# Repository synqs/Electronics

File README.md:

This project is licensed under the terms of the MIT license.

# Electronics in SynQS 

Here we have several electronics projects. Feel free to use and improve them.

## balancedphotodiode

It was used for a balanced PD design
in a polarization spectroscopy and worked fine. Designed initially by Lilo Höcker.

## simplePDboard

Just a simple board to have a transimpedence attached to the normal OSRAM PD.

## MagneticFieldSensor

We should add this here as it was the main project to the 18bit DAC and the 
digi-poti adapter. Designed initially by Marcell Gall.

## AOM_powersupply

A board which allows to drive a combination of VCO, attenuator, switch and amplifier. Designed initially by Pradyumna Paranjabe.

## shutter_board

A simple board to control a relay shutter. Designed initially by Pradyumna Paranjabe.

## others

the other projects were created before.

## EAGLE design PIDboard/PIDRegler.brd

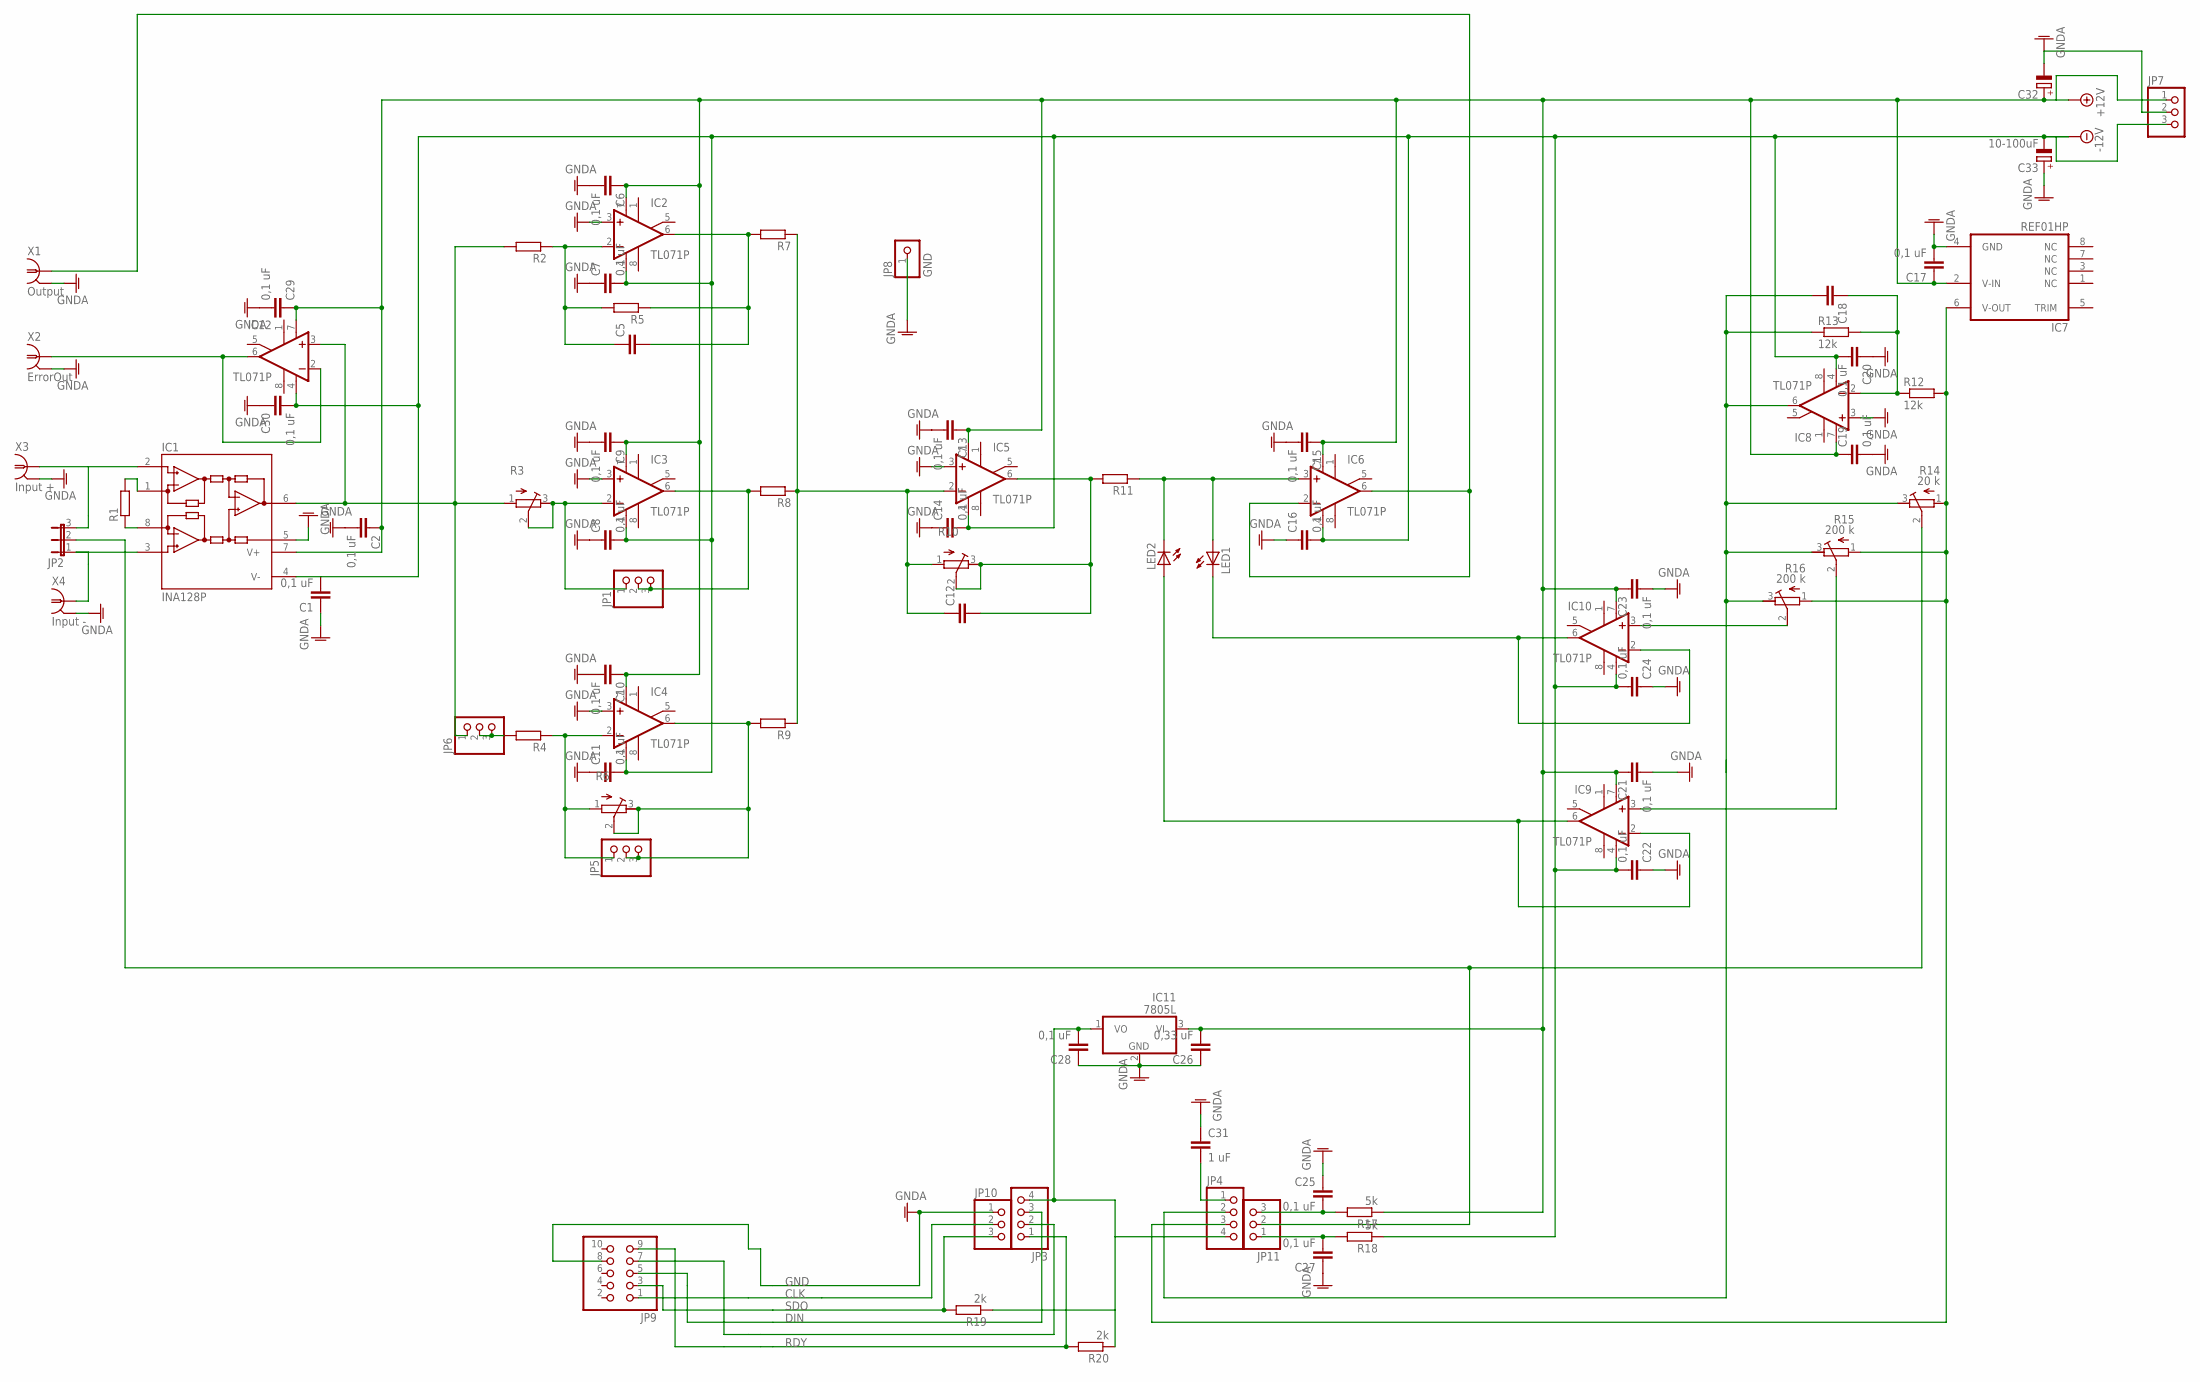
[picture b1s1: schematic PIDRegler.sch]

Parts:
C1, C2, C6, C7, C8, C9, C10, C11, C13, C14, C15, C16, C17, C19, C20, C21, C22, C23, C24, C25, C27, C28, C29, C30: 0,1 uF; C1206
C5, C12, C18: C-EUC1206; C1206
C26: 0,33 uF; C1206
C31: 1 uF; C1206
C32: CPOL-EUE2.5-6; E2,5-6
C33: 10-100uF; E2,5-6
IC1: INA128P; DIL08
IC2, IC3, IC4, IC5, IC6, IC8, IC9, IC10, IC12: TL071P; DIL08
IC7: REF01HP; DIL08
IC11: 7805L; TO92
JP1, JP5, JP6, JP7, JP10, JP11: PINHD-1X3; 1X03
JP2: JP2E; JP2
JP3, JP4: PINHD-1X4; 1X04
JP8: GND; 1X01
JP9: PINHD-2X5; 2X05
LED1, LED2: LED5MM
R1, R2, R4, R5, R7, R8, R9, R11: R-EU_M1206; M1206
R3, R6, R10: R-TRIMM64X; RTRIM64X
R12, R13: 12k; M1206
R14: 20 k; RTRIM64X
R15, R16: 200 k; RTRIM64X
R17, R18: 5k; M1206
R19, R20: 2k; M1206
X1: Output; AMP_227161
X2: ErrorOut; AMP_227161
X3: Input +; AMP_227161
X4: Input -; AMP_227161

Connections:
+12V: C2.1, C6.1, C9.1, C10.1, C13.1, C15.1, C17.1, C19.1, C21.1, C23.1, C26.2, C29.1, C32.+, IC1.7 (V+), IC2.7 (V+), IC3.7 (V+), IC4.7 (V+), IC5.7 (V+), IC6.7 (V+), IC7.2 (V-IN), IC8.7 (V+), IC9.7 (V+), IC10.7 (V+), IC11.3 (VI), IC12.7 (V+), JP7.1, R17.1
-12V: C1.2, C7.2, C8.2, C11.2, C14.2, C16.2, C20.2, C22.2, C24.2, C30.2, C33.-, IC1.4 (V-), IC2.4 (V-), IC3.4 (V-), IC4.4 (V-), IC5.4 (V-), IC6.4 (V-), IC8.4 (V-), IC9.4 (V-), IC10.4 (V-), IC12.4 (V-), JP7.3, R18.1
CLK: JP9.1, JP10.2
DIN: JP3.3, JP9.5
GND: C1.1, C2.2, C6.2, C7.1, C8.1, C9.2, C10.2, C11.1, C13.2, C14.1, C15.2, C16.1, C17.2, C19.2, C20.1, C21.2, C22.1, C23.2, C24.1, C25.1, C26.1, C27.1, C28.1, C29.2, C30.1, C31.1, C32.-, C33.+, IC1.5 (REF), IC2.3 (+IN), IC3.3 (+IN), IC4.3 (+IN), IC5.3 (+IN), IC7.4 (GND), IC8.3 (+IN), IC11.2 (GND), JP7.2, JP8.1, JP9.8, JP10.1, X1.2 (GND), X2.2 (GND), X3.2 (GND), X4.2 (GND)
unnamed: IC1.3 (+IN), JP2.1, X4.1
unnamed: IC1.8 (RG), R1.1
unnamed: IC1.1 (RG), R1.2
unnamed: IC1.2 (-IN), JP2.3, X3.1
unnamed: IC1.6 (OUT), IC12.3 (+IN), JP6.1, R2.2, R3.1 (E)
unnamed: IC3.2 (-IN), JP1.1, R3.2 (S), R3.3 (A)
unnamed: JP6.2, JP6.3, R4.2
unnamed: C5.1, IC2.2 (-IN), R2.1, R5.2
unnamed: C12.1, IC5.2 (-IN), R7.1, R8.1, R9.1, R10.1 (E)
unnamed: C5.2, IC2.6 (OUT), R5.1, R7.2
unnamed: IC3.6 (OUT), JP1.2, JP1.3, R8.2
unnamed: IC4.6 (OUT), JP5.2, JP5.3, R6.2 (S), R6.3 (A), R9.2
unnamed: C12.2, IC5.6 (OUT), R10.2 (S), R10.3 (A), R11.2
unnamed: IC6.2 (-IN), IC6.6 (OUT), X1.1
unnamed: IC7.6 (V-OUT), JP4.3, R12.2, R14.1 (E), R15.1 (E), R16.1 (E)
unnamed: JP2.2, JP11.2, R14.2 (S)
unnamed: C18.1, IC8.2 (-IN), R12.1, R13.2
unnamed: IC4.2 (-IN), JP5.1, R4.1, R6.1 (E)
unnamed: IC10.2 (-IN), IC10.6 (OUT), LED1.K (C)
unnamed: IC9.3 (+IN), R15.2 (S)
unnamed: IC9.2 (-IN), IC9.6 (OUT), LED2.A
unnamed: IC10.3 (+IN), R16.2 (S)
unnamed: IC6.3 (+IN), LED1.A, LED2.K (C), R11.1
unnamed: C31.2, JP4.1
unnamed: IC12.2 (-IN), IC12.6 (OUT), X2.1
unnamed: C18.2, IC8.6 (OUT), JP4.2, R13.1, R14.3 (A), R15.3 (A), R16.3 (A)
unnamed: C25.2, JP11.3, R17.2
unnamed: C27.2, JP11.1, R18.2
RDY: JP3.1, JP9.9, R20.2
SDO: JP9.3, JP10.3, R19.2
SYNC: JP3.2, JP9.7
VCC: C28.2, IC11.1 (VO), JP3.4, JP4.4, R19.1, R20.1

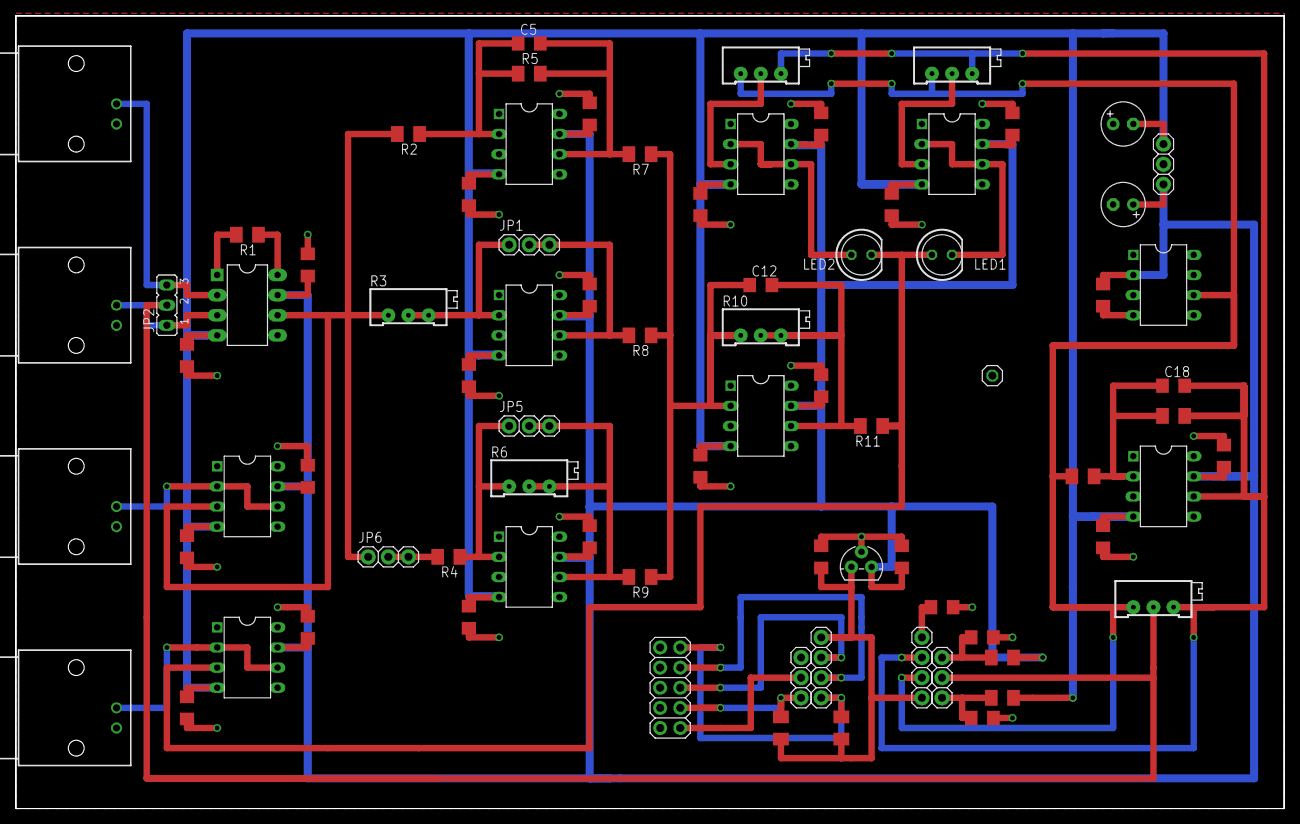
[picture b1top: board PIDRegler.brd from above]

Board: 2 copper layers, 160.0 x 100.0 mm, 80 parts (0 on the bottom side), 37 nets.

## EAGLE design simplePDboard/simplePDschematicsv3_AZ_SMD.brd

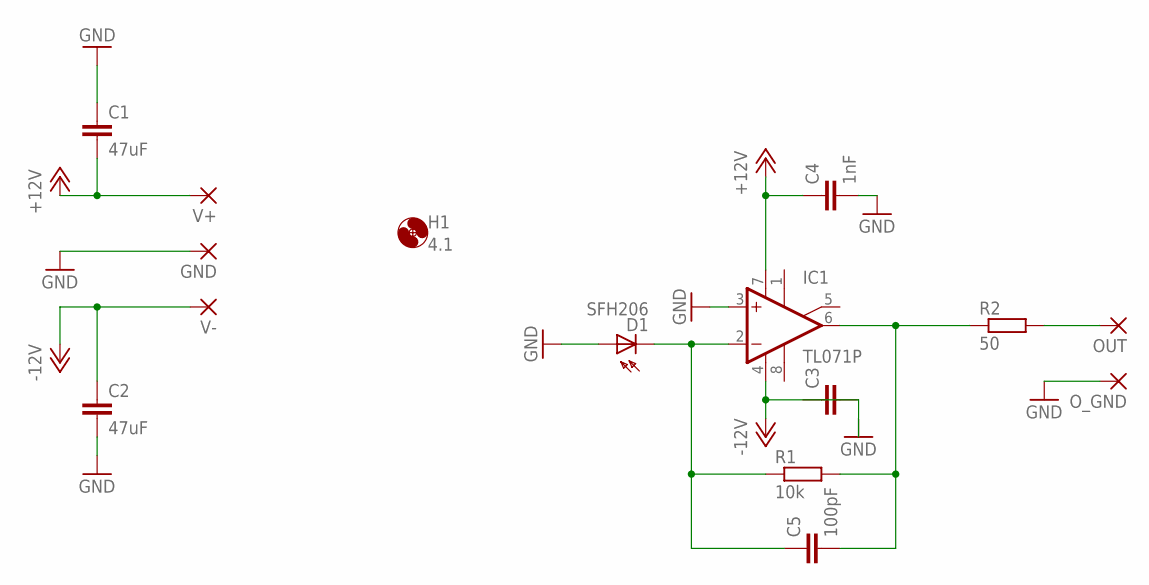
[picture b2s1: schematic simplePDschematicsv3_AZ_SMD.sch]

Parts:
C1, C2: 47uF; C050-075X075
C3: C-EUC0504; C0504
C4: 1nF; C025-050X050
C5: 100pF; C025-050X050
D1: SFH206
GND: 1,6/0,9
H1: 4.1; 4,1
IC1: TL071P; DIL08
OUT: 1,6/0,9
O_GND: 1,6/0,9
R1: 10k; M1206
R2: 50; M1206
V+: 1,6/0,9
V-: 1,6/0,9

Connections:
GND: C1.1, C2.2, C4.2, D1.A, GND.1, IC1.3 (+IN), O_GND.1
unnamed: OUT.1, R2.2
unnamed: C5.2, IC1.6 (OUT), R1.2, R2.1
unnamed: C5.1, D1.K (C), IC1.2 (-IN), R1.1
V+: C1.2, C4.1, IC1.7 (V+), V+.1
V-: C2.1, IC1.4 (V-), V-.1

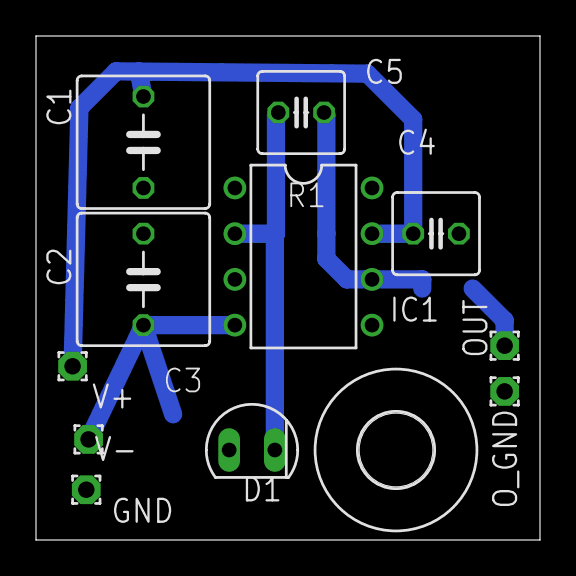
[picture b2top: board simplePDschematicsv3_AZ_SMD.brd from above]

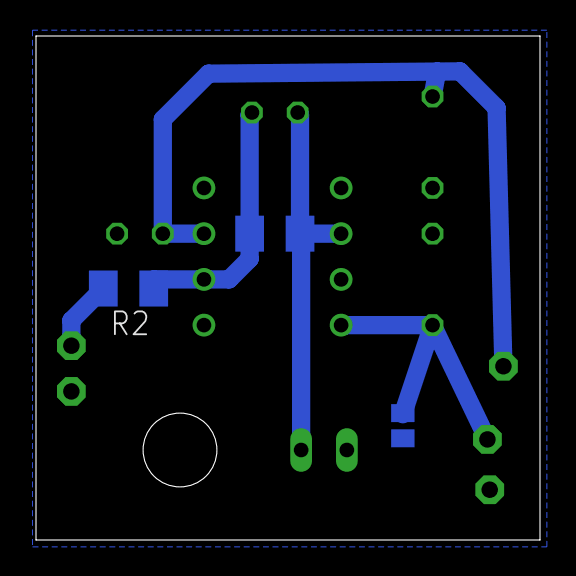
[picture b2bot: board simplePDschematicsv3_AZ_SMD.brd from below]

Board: 2 copper layers, 28.0 x 28.0 mm, 15 parts (3 on the bottom side), 6 nets.

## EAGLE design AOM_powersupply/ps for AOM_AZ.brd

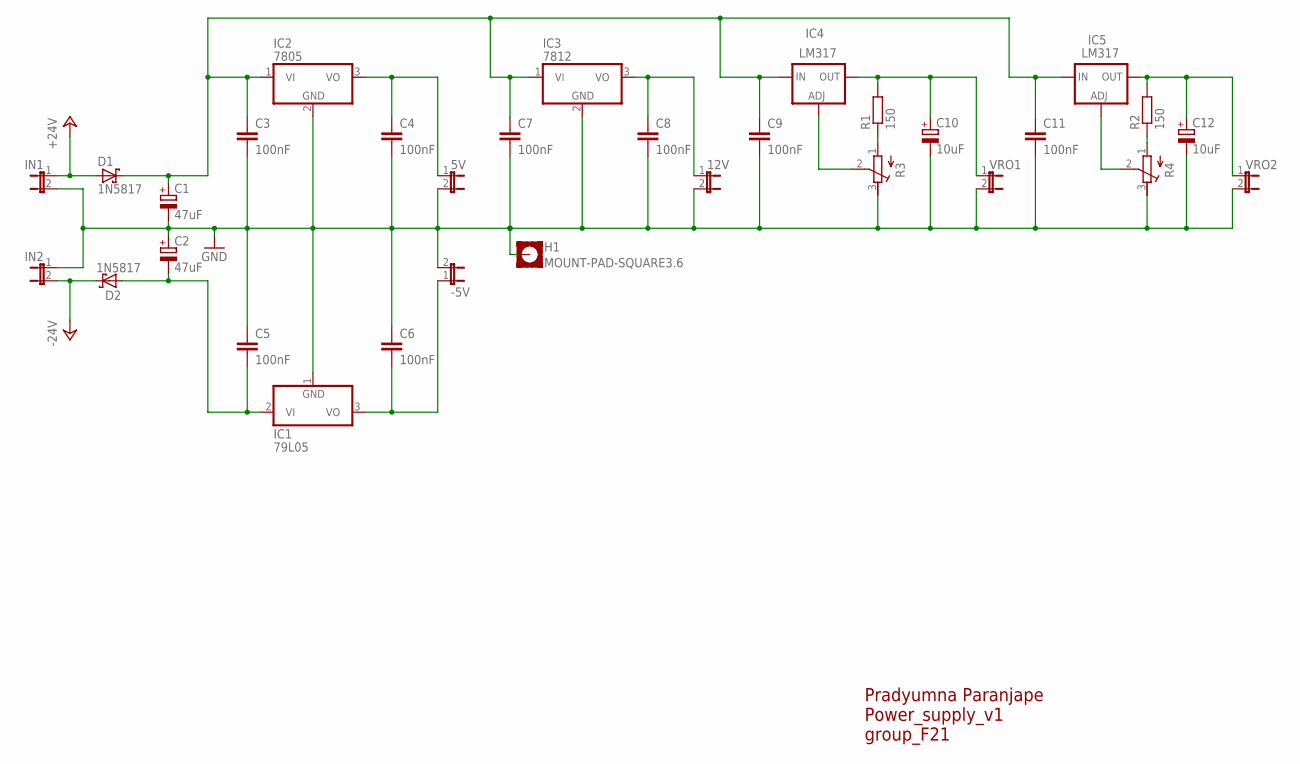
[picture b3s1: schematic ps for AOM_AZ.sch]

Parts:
5V, 12V: JP1E; JP1
-5V: JP1E; JP1
C1, C2: 47uF; E5-6
C3, C4, C5, C6, C7, C8, C9, C11: 100nF; C1206K
C10, C12: 10uF; E1,8-4
D1, D2: 1N5817; DO41-7.6
H1: MOUNT-PAD-SQUARE3.6; 3,6-PAD-SQUARE
IC1: 79L05; TO92
IC2: 7805; TO220H
IC3: 7812; TO220H
IC4, IC5: LM317; TO220H
IN1, IN2: JP1E; JP1
R1, R2: 150; R1206
R3, R4: R-TRIMM3296Y; RTRIM3296Y
VRO1, VRO2: JP1E; JP1

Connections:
+24V: D1.A, IN1.1
+VS: C1.+, C3.1, C7.1, C9.1, C11.1, D1.C, IC2.1 (VI), IC3.1 (VI), IC4.3 (IN), IC5.3 (IN)
-24V: D2.C, IN2.2
-VS: C2.-, C5.2, D2.A, IC1.2 (VI)
GND: 5V.2, 12V.2, -5V.2, C1.-, C2.+, C3.2, C4.2, C5.1, C6.1, C7.2, C8.2, C9.2, C10.-, C11.2, C12.-, H1.B3,6, IC1.1 (GND), IC2.2 (GND), IC3.2 (GND), IN1.2, IN2.1, R3.3 (E), R4.3 (E), VRO1.2, VRO2.2
unnamed: C12.+, IC5.2 (OUT), R2.2, VRO2.1
unnamed: 12V.1, C8.1, IC3.3 (VO)
unnamed: 5V.1, C4.1, IC2.3 (VO)
unnamed: -5V.1, C6.2, IC1.3 (VO)
unnamed: R1.1, R3.1 (A)
unnamed: IC4.1 (ADJ), R3.2 (S)
unnamed: C10.+, IC4.2 (OUT), R1.2, VRO1.1
unnamed: R2.1, R4.1 (A)
unnamed: IC5.1 (ADJ), R4.2 (S)

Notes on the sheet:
Pradyumna Paranjape Power_supply_v1 group_F21

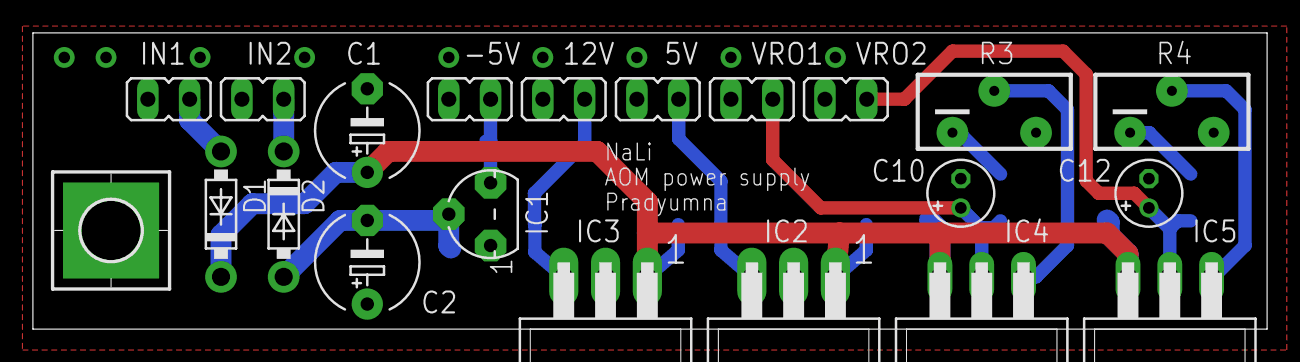
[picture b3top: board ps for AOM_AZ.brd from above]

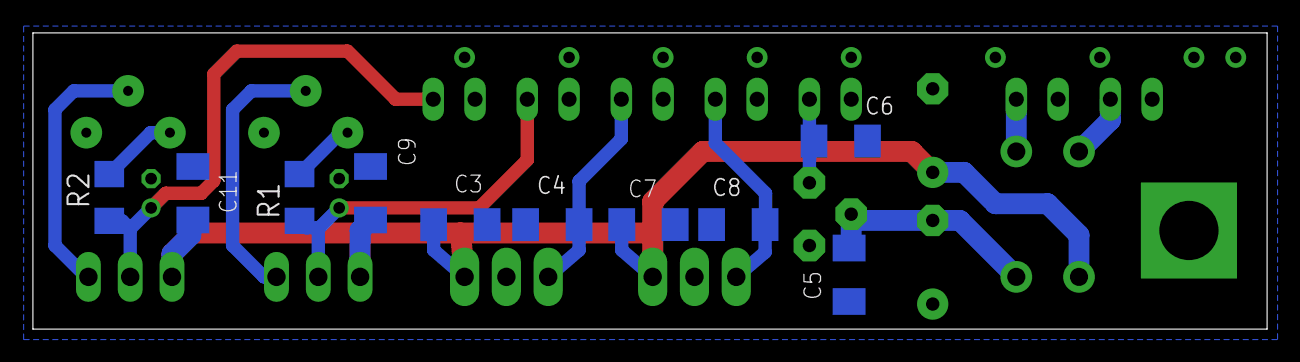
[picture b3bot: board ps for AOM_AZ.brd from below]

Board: 2 copper layers, 75.0 x 18.0 mm, 31 parts (10 on the bottom side), 14 nets.

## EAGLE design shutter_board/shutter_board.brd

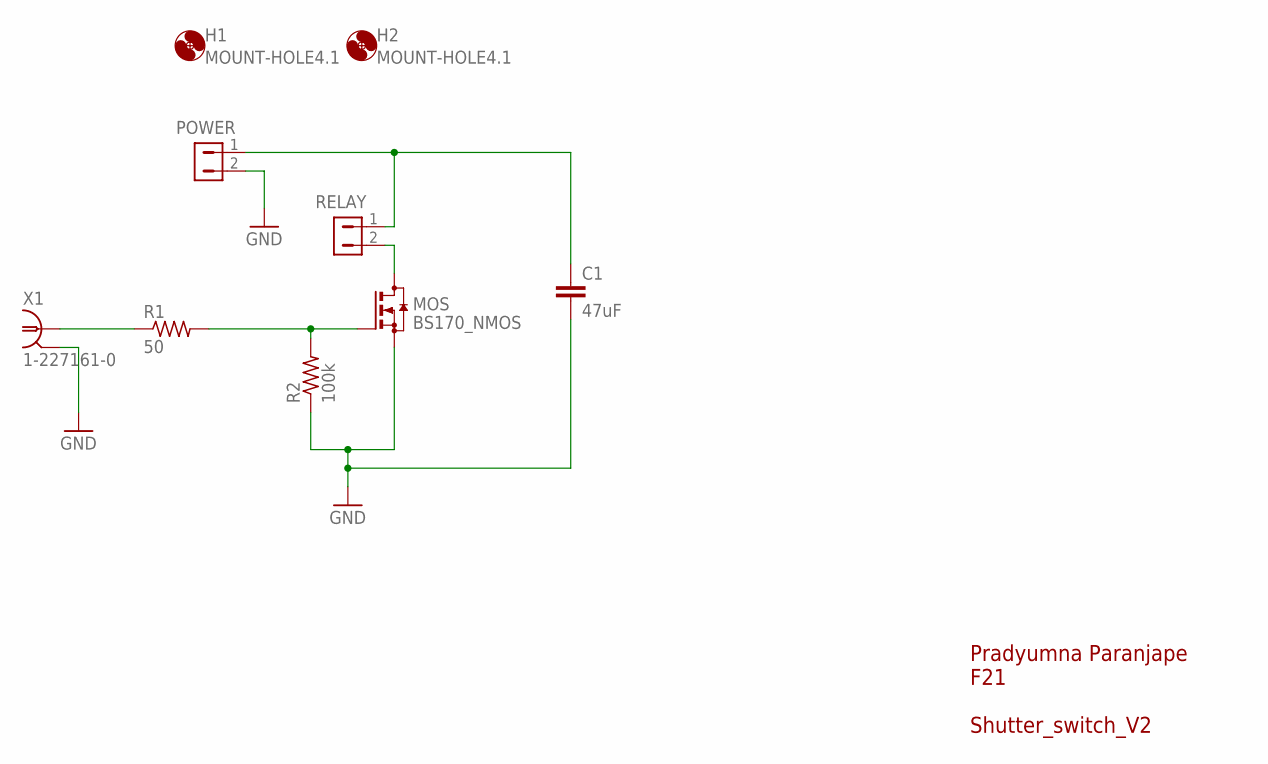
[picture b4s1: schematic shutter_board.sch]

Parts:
C1: 47uF; NALI_CAP
H1, H2: MOUNT-HOLE4.1; 4,1
MOS: BS170_NMOS; TO92-3
POWER: 2PIN_CONNECTOR; KK2_MOLEX
R1: 50; SMALL_RESIS
R2: 100k; SMALL_RESIS
RELAY: 2PIN_CONNECTOR; KK2_MOLEX
X1: 1-227161-0; AMP_227161

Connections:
GND: C1.2, MOS.3 (S), POWER.2 (4), R2.1, X1.2
unnamed: R1.1, X1.1
unnamed: MOS.2 (G), R1.2, R2.2
unnamed: C1.1, POWER.1 (2), RELAY.1 (2)
unnamed: MOS.1 (D), RELAY.2 (4)

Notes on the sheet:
Pradyumna Paranjape F21 Shutter_switch_V2

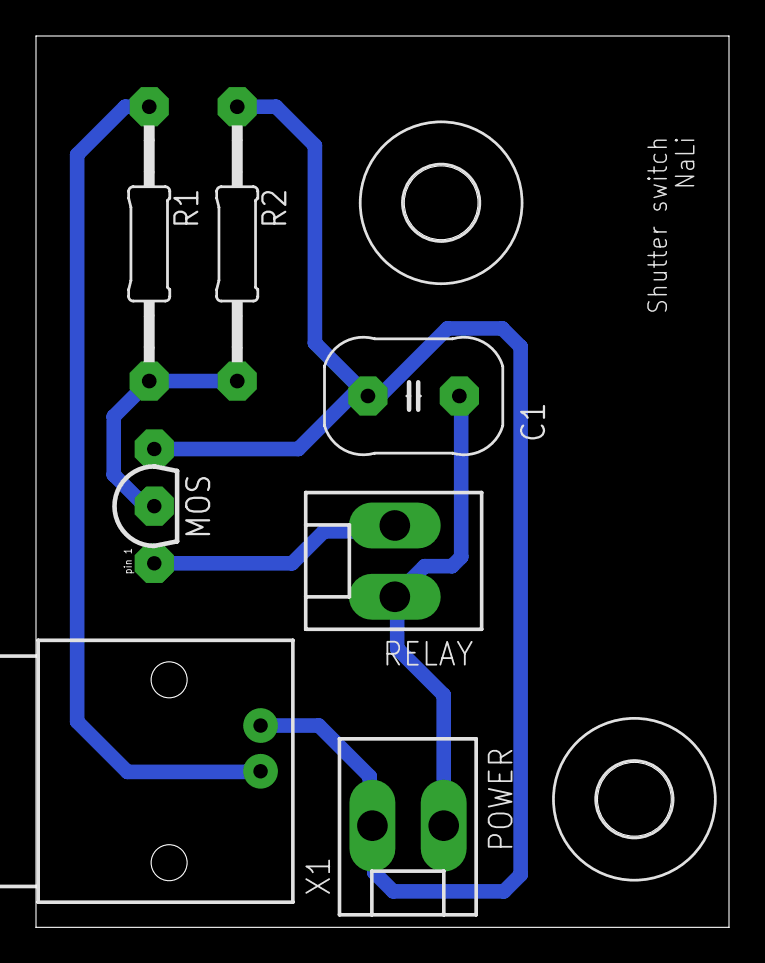
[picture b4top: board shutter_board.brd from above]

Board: 2 copper layers, 38.5 x 49.5 mm, 9 parts (0 on the bottom side), 5 nets.

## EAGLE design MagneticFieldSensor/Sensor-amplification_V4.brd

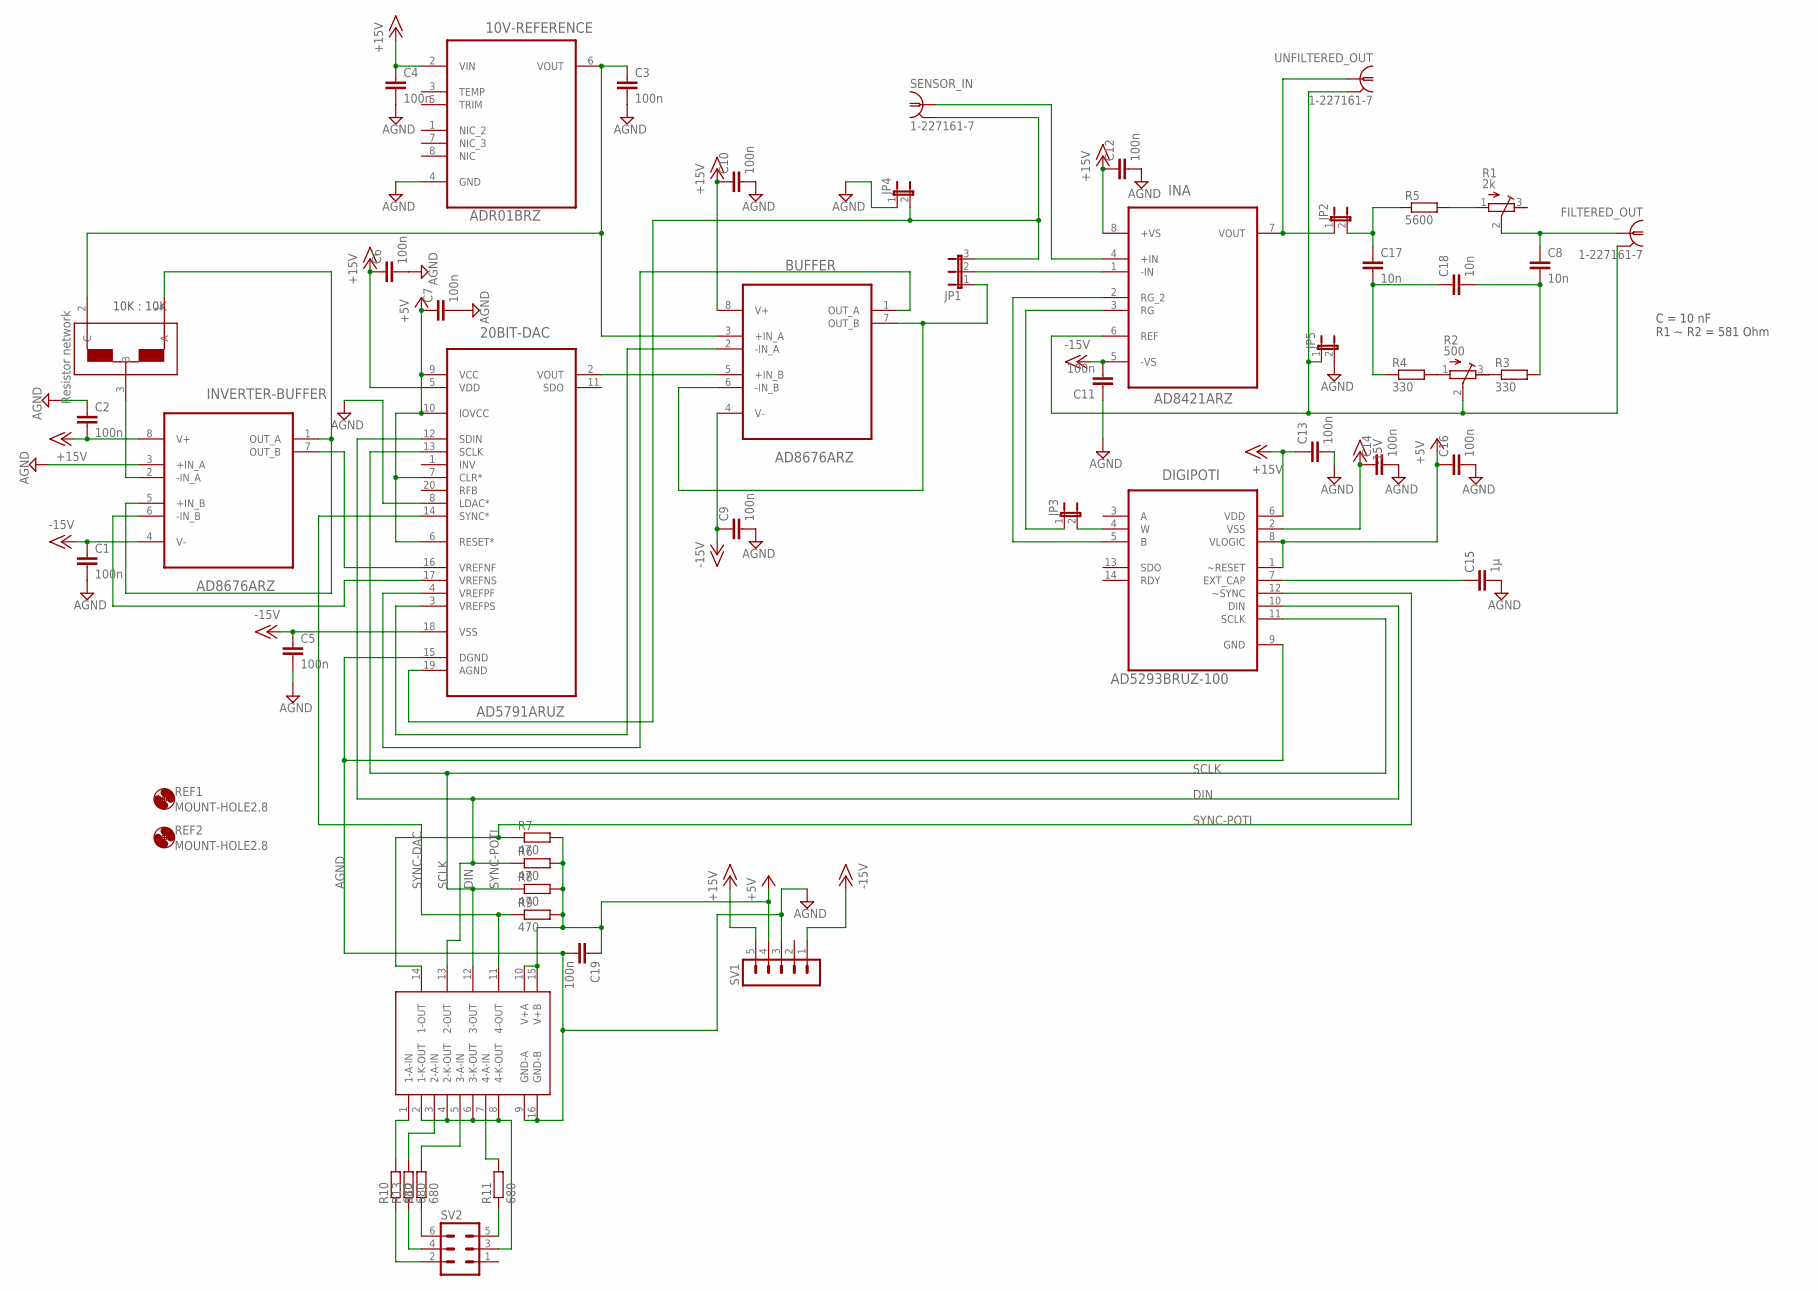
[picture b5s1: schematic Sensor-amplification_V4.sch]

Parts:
10V-REFERENCE: ADR01BRZ; SOIC127P600X175-8N
20BIT-DAC: AD5791ARUZ; SOP65P640X120-20N
BUFFER: AD8676ARZ; SOIC127P600X175-8N
C1, C2, C3, C4, C5, C6, C7, C9, C10, C11, C12, C13, C14, C16, C19: 100n; C0603
C8, C17, C18: 10n; C0805
C15: 1µ; C0603
DIGIPOTI: AD5293BRUZ-100; SOP65P640X120-14N
FILTERED_OUT: 1-227161-7; AMP_227161
INA: AD8421ARZ; SOIC127P600X175-8N
INVERTER-BUFFER: AD8676ARZ; SOIC127P600X175-8N
JP1: JP2E; JP2
JP2, JP3, JP4, JP5: JP1E; JP1
OPTOCOUPLER: ACSL-6400; SO16
R1: 2k; RTRIM64W
R2: 500; RTRIM64W
R3, R4: 330; M1206
R5: 5600; M1206
R6, R7, R8, R9: 470; M1206
R10, R11, R12, R13: 680; M1206
R20: MPMT2001AT5; SOT23
REF1, REF2: MOUNT-HOLE2.8; 2,8
SENSOR_IN: 1-227161-7; AMP_227161
SV1: MA05-1
SV2: MA03-2
UNFILTERED_OUT: 1-227161-7; AMP_227161

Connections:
+5V: 20BIT-DAC.6 (RESET*), 20BIT-DAC.7 (CLR*), 20BIT-DAC.9 (VCC), 20BIT-DAC.10 (IOVCC), C7.1, C16.1, C19.1, DIGIPOTI.1 (~RESET), DIGIPOTI.8 (VLOGIC), OPTOCOUPLER.10 (V+A), OPTOCOUPLER.15 (V+B), R6.2, R7.2, R8.2, R9.2, SV1.4
+15V: 10V-REFERENCE.2 (VIN), 20BIT-DAC.5 (VDD), BUFFER.8 (V+), C2.2, C4.1, C6.1, C10.1, C12.1, C13.1, DIGIPOTI.6 (VDD), INA.8 (+VS), INVERTER-BUFFER.8 (V+), SV1.5
-15V: 20BIT-DAC.18 (VSS), BUFFER.4 (V-), C1.1, C5.1, C9.1, C11.2, C14.1, DIGIPOTI.2 (VSS), INA.5 (-VS), INVERTER-BUFFER.4 (V-), SV1.1
AGND: 10V-REFERENCE.4 (GND), 20BIT-DAC.8 (LDAC*), 20BIT-DAC.15 (DGND), C1.2, C2.1, C3.2, C4.2, C5.2, C6.2, C7.2, C9.2, C10.2, C11.1, C12.2, C13.2, C14.2, C15.2, C16.2, C19.2, DIGIPOTI.9 (GND), INVERTER-BUFFER.3 (+IN_A), JP4.1, JP5.2, OPTOCOUPLER.9 (GND-A), OPTOCOUPLER.16 (GND-B), SV1.3
DIN: 20BIT-DAC.12 (SDIN), DIGIPOTI.10 (DIN), OPTOCOUPLER.13 (2-OUT), R6.1
unnamed: INA.7 (VOUT), JP2.1, UNFILTERED_OUT.1
unnamed: FILTERED_OUT.2, INA.6 (REF), JP5.1, R2.2 (S), UNFILTERED_OUT.2
unnamed: INA.3 (RG), JP3.1
unnamed: DIGIPOTI.5 (B), INA.2 (RG_2)
unnamed: INA.4 (+IN), SENSOR_IN.1
unnamed: 20BIT-DAC.19 (AGND), JP1.3, JP4.2, SENSOR_IN.2
unnamed: INA.1 (-IN), JP1.2
unnamed: DIGIPOTI.4 (W), JP3.2
unnamed: 10V-REFERENCE.6 (VOUT), BUFFER.3 (+IN_A), C3.1, R20.2 (C)
unnamed: 20BIT-DAC.2 (VOUT), BUFFER.5 (+IN_B)
unnamed: 20BIT-DAC.4 (VREFPF), BUFFER.1 (OUT_A)
unnamed: 20BIT-DAC.3 (VREFPS), BUFFER.2 (-IN_A)
unnamed: INVERTER-BUFFER.2 (-IN_A), R20.3 (B)
unnamed: 20BIT-DAC.16 (VREFNF), INVERTER-BUFFER.7 (OUT_B)
unnamed: 20BIT-DAC.17 (VREFNS), INVERTER-BUFFER.6 (-IN_B)
unnamed: INVERTER-BUFFER.1 (OUT_A), INVERTER-BUFFER.5 (+IN_B), R20.1 (A)
unnamed: C15.1, DIGIPOTI.7 (EXT_CAP)
unnamed: C17.2, C18.1, R4.1
unnamed: C8.2, C18.2, R3.2
unnamed: C8.1, FILTERED_OUT.1, R1.2 (S)
unnamed: C17.1, JP2.2, R5.1
unnamed: R2.3 (E), R3.1
unnamed: R2.1 (A), R4.2
unnamed: R1.1 (A), R5.2
unnamed: OPTOCOUPLER.2 (1-K-OUT), OPTOCOUPLER.4 (2-K-OUT), OPTOCOUPLER.6 (3-K-OUT), OPTOCOUPLER.8 (4-K-OUT), SV2.3
unnamed: OPTOCOUPLER.7 (4-A-IN), R11.2
unnamed: OPTOCOUPLER.5 (3-A-IN), R12.2
unnamed: OPTOCOUPLER.3 (2-A-IN), R13.2
unnamed: R10.1, SV2.2
unnamed: OPTOCOUPLER.1 (1-A-IN), R10.2
unnamed: R13.1, SV2.4
unnamed: R12.1, SV2.6
unnamed: R11.1, SV2.5
SCLK: 20BIT-DAC.13 (SCLK), DIGIPOTI.11 (SCLK), OPTOCOUPLER.12 (3-OUT), R8.1
SUBSTRACT_SELECT: BUFFER.6 (-IN_B), BUFFER.7 (OUT_B), JP1.1
SYNC-DAC: 20BIT-DAC.14 (SYNC*), OPTOCOUPLER.11 (4-OUT), R9.1
SYNC-POTI: DIGIPOTI.12 (~SYNC), OPTOCOUPLER.14 (1-OUT), R7.1

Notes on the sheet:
10K : 10K
C = 10 nF R1 ~ R2 = 581 Ohm

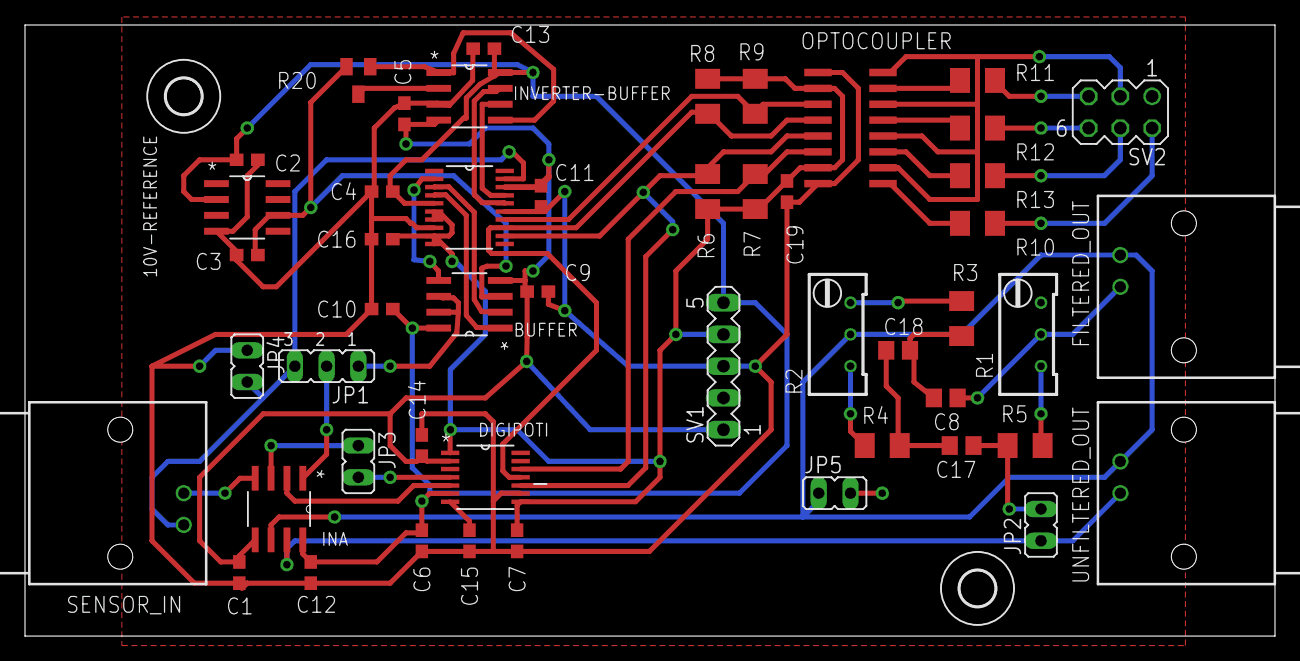
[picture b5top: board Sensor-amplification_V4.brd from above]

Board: 2 copper layers, 100.0 x 48.9 mm, 52 parts (0 on the bottom side), 42 nets.

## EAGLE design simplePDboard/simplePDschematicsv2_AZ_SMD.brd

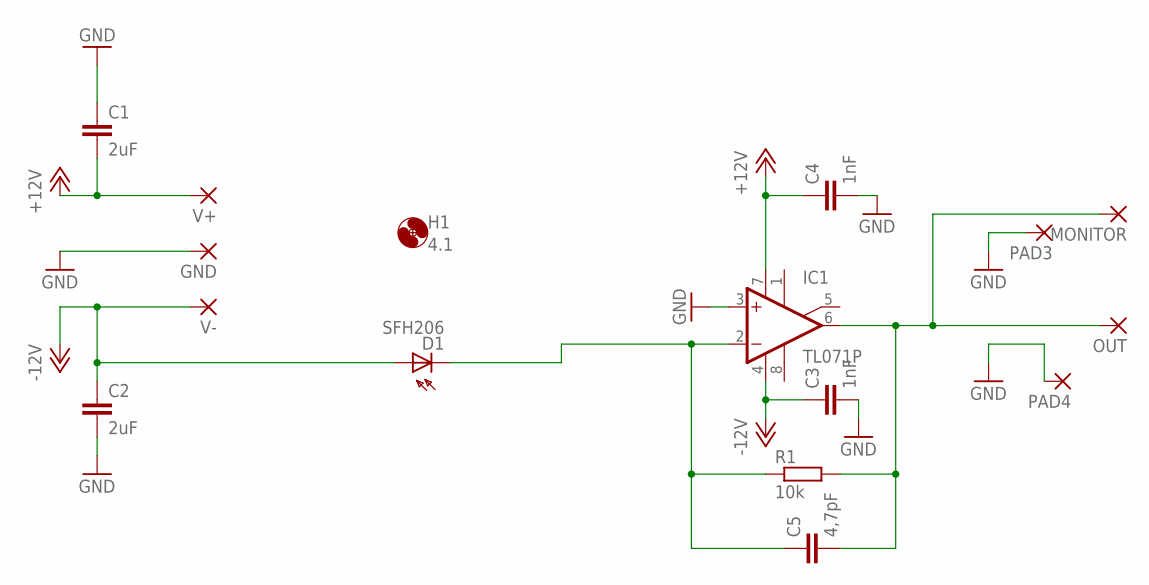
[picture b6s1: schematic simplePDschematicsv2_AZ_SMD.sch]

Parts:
C1, C2: 2uF; C050-075X075
C3, C4: 1nF; C025-050X050
C5: 4,7pF; C025-050X050
D1: SFH206
GND: 1,6/0,9
H1: 4.1; 4,1
IC1: TL071P; DIL08
MONITOR: 1,6/0,9
OUT: 1,6/0,9
PAD3, PAD4: 1,6/0,9
R1: 10k; M1206
V+: 1,6/0,9
V-: 1,6/0,9

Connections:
GND: C1.1, C2.2, C3.2, C4.2, GND.1, IC1.3 (+IN), PAD3.1, PAD4.1
unnamed: C5.2, IC1.6 (OUT), MONITOR.1, OUT.1, R1.2
unnamed: C5.1, D1.K (C), IC1.2 (-IN), R1.1
V+: C1.2, C4.1, IC1.7 (V+), V+.1
V-: C2.1, C3.1, D1.A, IC1.4 (V-), V-.1

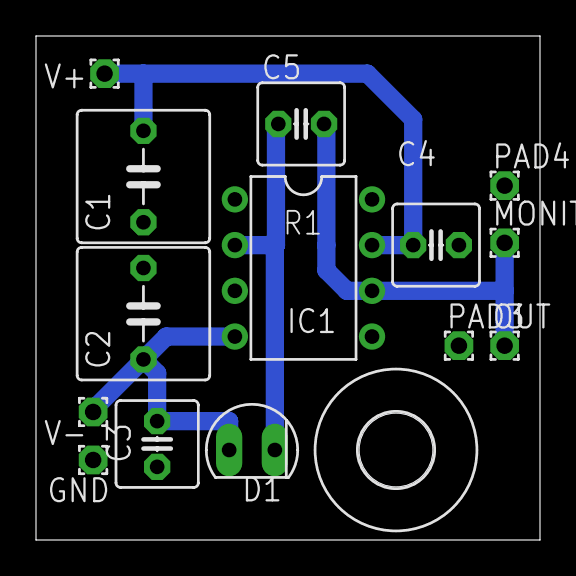
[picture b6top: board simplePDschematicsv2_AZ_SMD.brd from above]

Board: 1 copper layer, 28.0 x 28.0 mm, 16 parts (1 on the bottom side), 5 nets.

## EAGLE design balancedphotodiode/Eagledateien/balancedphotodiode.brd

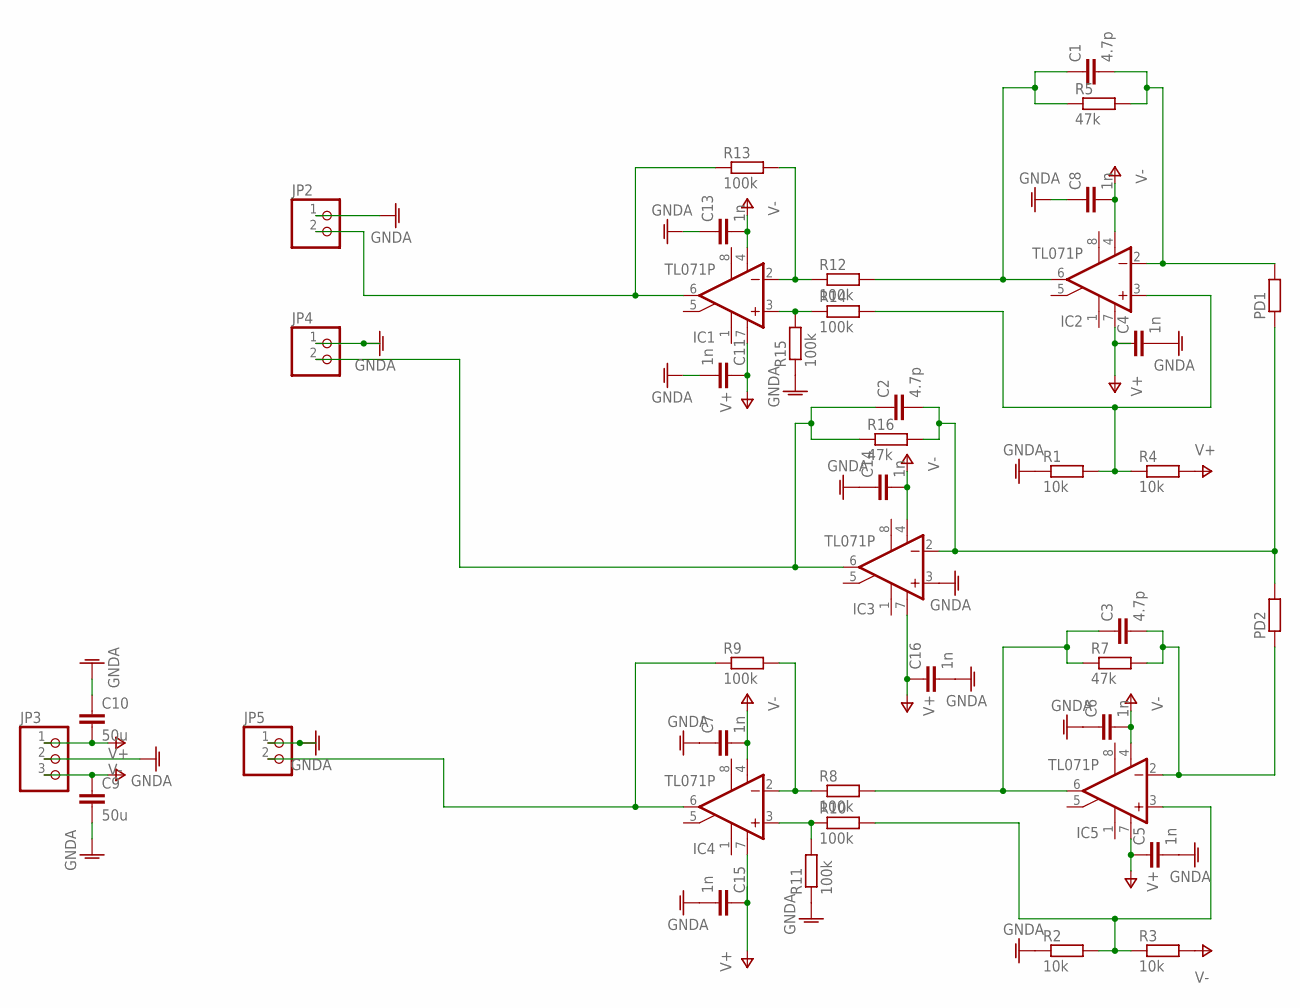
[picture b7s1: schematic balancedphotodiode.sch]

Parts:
C1, C2, C3: 4.7p; C025-024X044
C4, C5, C6, C7, C8, C11, C13, C14, C15, C16: 1n; C1206
C9, C10: 50u; C025-050X050
IC1, IC2, IC3, IC4, IC5: TL071P; DIL08
JP2, JP4, JP5: PINHD-1X2/90; 1X02/90
JP3: PINHD-1X3/90; 1X03/90
PD1, PD2: R-EU_0204/2V; 0204V
R1, R2, R3, R4: 10k; 0207/7
R5, R7, R16: 47k; 0207/7
R8, R9, R10, R11, R12, R13, R14, R15: 100k; 0207/7

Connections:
GNDA: C4.2, C5.2, C6.1, C7.1, C8.1, C9.2, C10.1, C11.2, C13.1, C14.1, C15.2, C16.2, IC3.3 (+IN), JP2.1, JP3.2, JP4.1, JP5.1, R1.1, R2.1, R11.1, R15.1
unnamed: C1.2, IC2.2 (-IN), PD1.2, R5.2
unnamed: C1.1, IC2.6 (OUT), R5.1, R12.2
unnamed: C2.2, IC3.2 (-IN), PD1.1, PD2.2, R16.2
unnamed: C3.2, IC5.2 (-IN), PD2.1, R7.2
unnamed: C3.1, IC5.6 (OUT), R7.1, R8.2
unnamed: C2.1, IC3.6 (OUT), JP4.2, R16.1
unnamed: IC1.2 (-IN), R12.1, R13.2
unnamed: IC4.2 (-IN), R8.1, R9.2
unnamed: IC1.6 (OUT), JP2.2, R13.1
unnamed: IC4.6 (OUT), JP5.2, R9.1
unnamed: IC5.3 (+IN), R2.2, R3.1, R10.2
unnamed: IC4.3 (+IN), R10.1, R11.2
unnamed: IC1.3 (+IN), R14.1, R15.2
unnamed: IC2.3 (+IN), R1.2, R4.1, R14.2
V+: C4.1, C5.1, C9.1, C11.1, C15.1, C16.1, IC1.7 (V+), IC2.7 (V+), IC3.7 (V+), IC4.7 (V+), IC5.7 (V+), JP3.3, R4.2
V-: C6.2, C7.2, C8.2, C10.2, C13.2, C14.2, IC1.4 (V-), IC2.4 (V-), IC3.4 (V-), IC4.4 (V-), IC5.4 (V-), JP3.1, R3.2

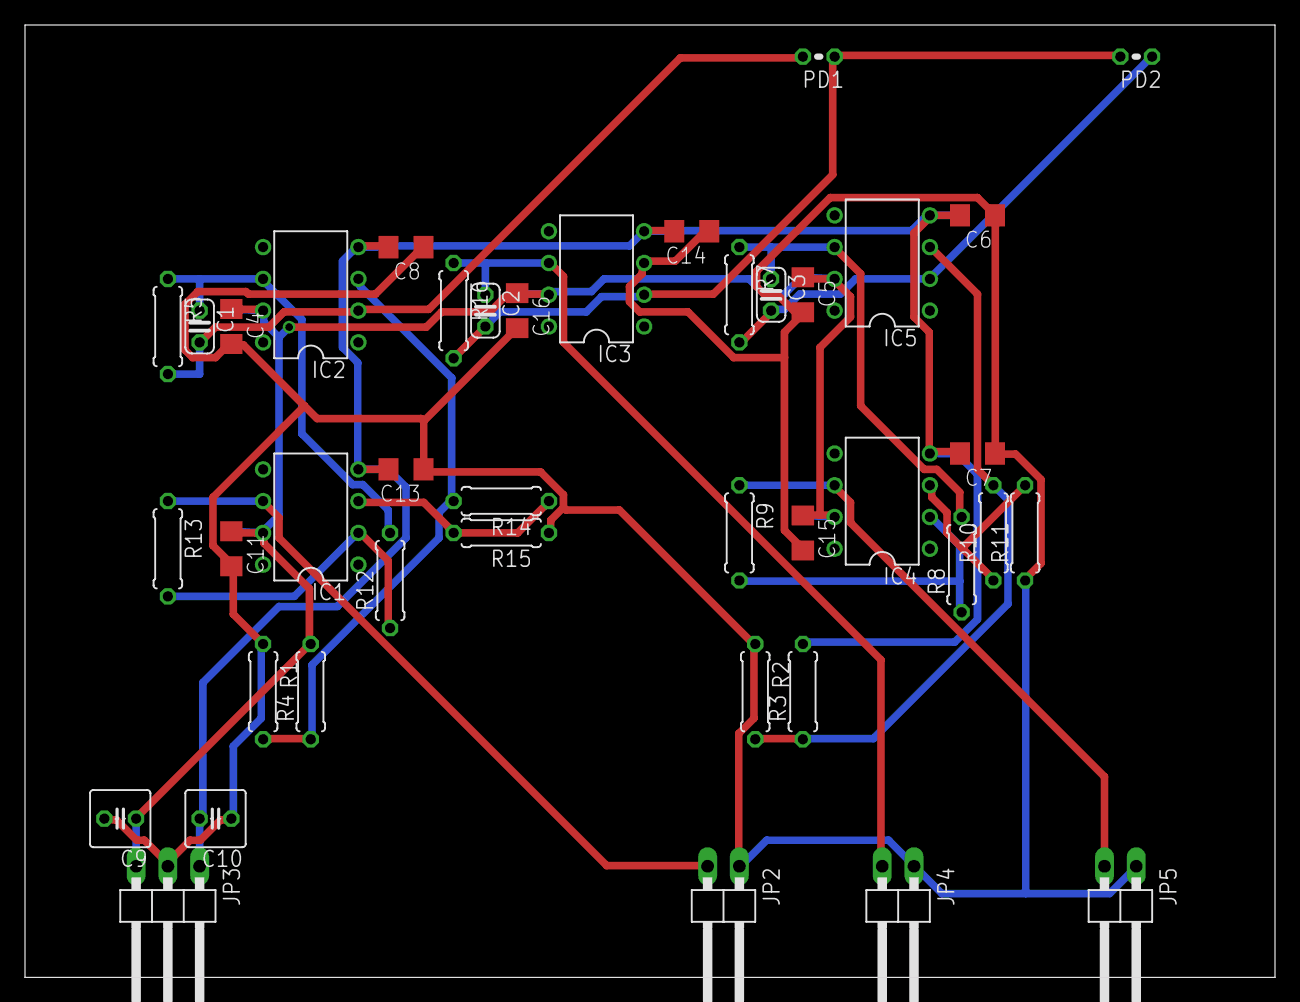
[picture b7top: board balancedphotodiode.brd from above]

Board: 2 copper layers, 100.0 x 76.2 mm, 41 parts (0 on the bottom side), 17 nets.
